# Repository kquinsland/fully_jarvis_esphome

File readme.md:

# Jarvis ESPHome

This is an extension / port of the initial reverse engineering work done by [@phord](https://github.com/phord) for the [`Jarvis`](https://github.com/phord/Jarvis) repo.
Rather than build everything from scratch, I have ported most of the functionality to an ESPHome component.

**Note:** You almost certainly should not use this ESPHome component! Thanks to [@maraid](https://github.com/maraid), more of the [UART has been reverse engineered](https://github.com/maraid/Jarvis#technical-notes). This means that the PCB is out of date and can be re-factored to simply interface with the desk via UART. This theoretically also means that ESPHome can control more aspects of the desk more precisely with fewer wires and a simpler software implementation!

## ESPHome Component

I am not a full time C++ programmer so the code almost certainly does look like a bad copy/paste job.
That's because it largely is! I found a few different "similar" projects and modeled my code off of those.

Details on how to use the custom component with ESPHome can be found in [components/fully_jarvis_cb2c](components/fully_jarvis_cb2c).

## PCB

Inspired by [this](https://github.com/phord/Jarvis/discussions/18) thread, I created a simple PCB to interface with the desk control / motor driver.
I used a more capable ESP32 module specifically so I could drive some RGBWW LED strips as well.

See the [cad](cad/readme.md) folder for the KiCad files.

The (mostly populated) PCB looks like this:

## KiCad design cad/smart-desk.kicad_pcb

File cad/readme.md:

# smart-desk-pcb

If you want to edit the pcb, the KiCad 6 files are included subject to [the license terms](../LICENSE.md).

The ESP32 module comes from [this](https://github.com/r0oland/ESP32_mini_KiCad_Library) library. Thanks to [r0oland](https://github.com/r0oland) for that library!

## BOM

The primary components on the PCB are:

- [D1 Mini style ESP32 chip](https://www.aliexpress.com/item/2251832633593063.html)
- [Configurable DC Buck converter module](https://www.aliexpress.com/item/32833398811.html). This steps the 12V dc from the KVM power supply down to the 5V for the ESP32 module.
- [RJ45 Jack (LCSC: C385834)](https://lcsc.com/product-detail/Ethernet-Connectors-Modular-Connectors-RJ45-RJ11_Ckmtw-Shenzhen-Cankemeng-R-RJ45R08P-A004_C385834.html). Footprint for this should be included in `jlcpcb.kicad_sym`. Two of theses for easy connection to the Jarvis remote/motor-controller.
- 2x5 ct [Diodes Incorporated DMN1019USN-7 (LCSC: C145103)](https://lcsc.com/product-detail/MOSFETs_Diodes-Incorporated-DMN1019USN-7_C145103.html). I had these handy and with the current ship shortage, it didn't seem worth th effort to try to source better ones. These are optional if you don't want the LED portion of the PCB.
- [Fuse holder (LCSC:C3131)](https://lcsc.com/product-detail/Fuse-Holders_Xucheng-Elec-C3131_C3131.html). Jump this out at your own risk!

There are some additional headers on the PCB for some optional components:

- PIR sensor (wired to ESP `gpio39`). I ended up not using this as I already have sufficient presence detection through other sensors placed around my home.
- An i2c based LIDAR sensor [`tof10120`](https://esphome.io/components/sensor/tof10120.html)) which I am using to measure distance from the desk to chair/person. Inclusion of this sensor was inspired by [this](.https://www.thouters.be/Standingstats.html) post from `Thomas Langewouters`.

## gerber

If you want to make zero changes, the [gerber files are included](./exports/2022-03.26.zip) and are subject to [the license terms](../LICENSE.md).

**Note**: There is a _small_ 'bug' with the v1 PCB: some of the MOSFETS do not have a connection to the ground plain. No, I don't know how this passed DRC. Fortunately, the fix is pretty easy: two small bodge wires connecting the GND pin from `U11` and `U15` to vias which connect to the ground plane.

**Note:** the two grey wires next to the fuse holder.

The gerber files / KiCad project are set up for use with JLCPCB but probably would work as-is with other PCB fab houses, too.

## Enclosure

I have included a STEP file export of the v1 PCB should you need it for PCB mounting hole locations or similar.

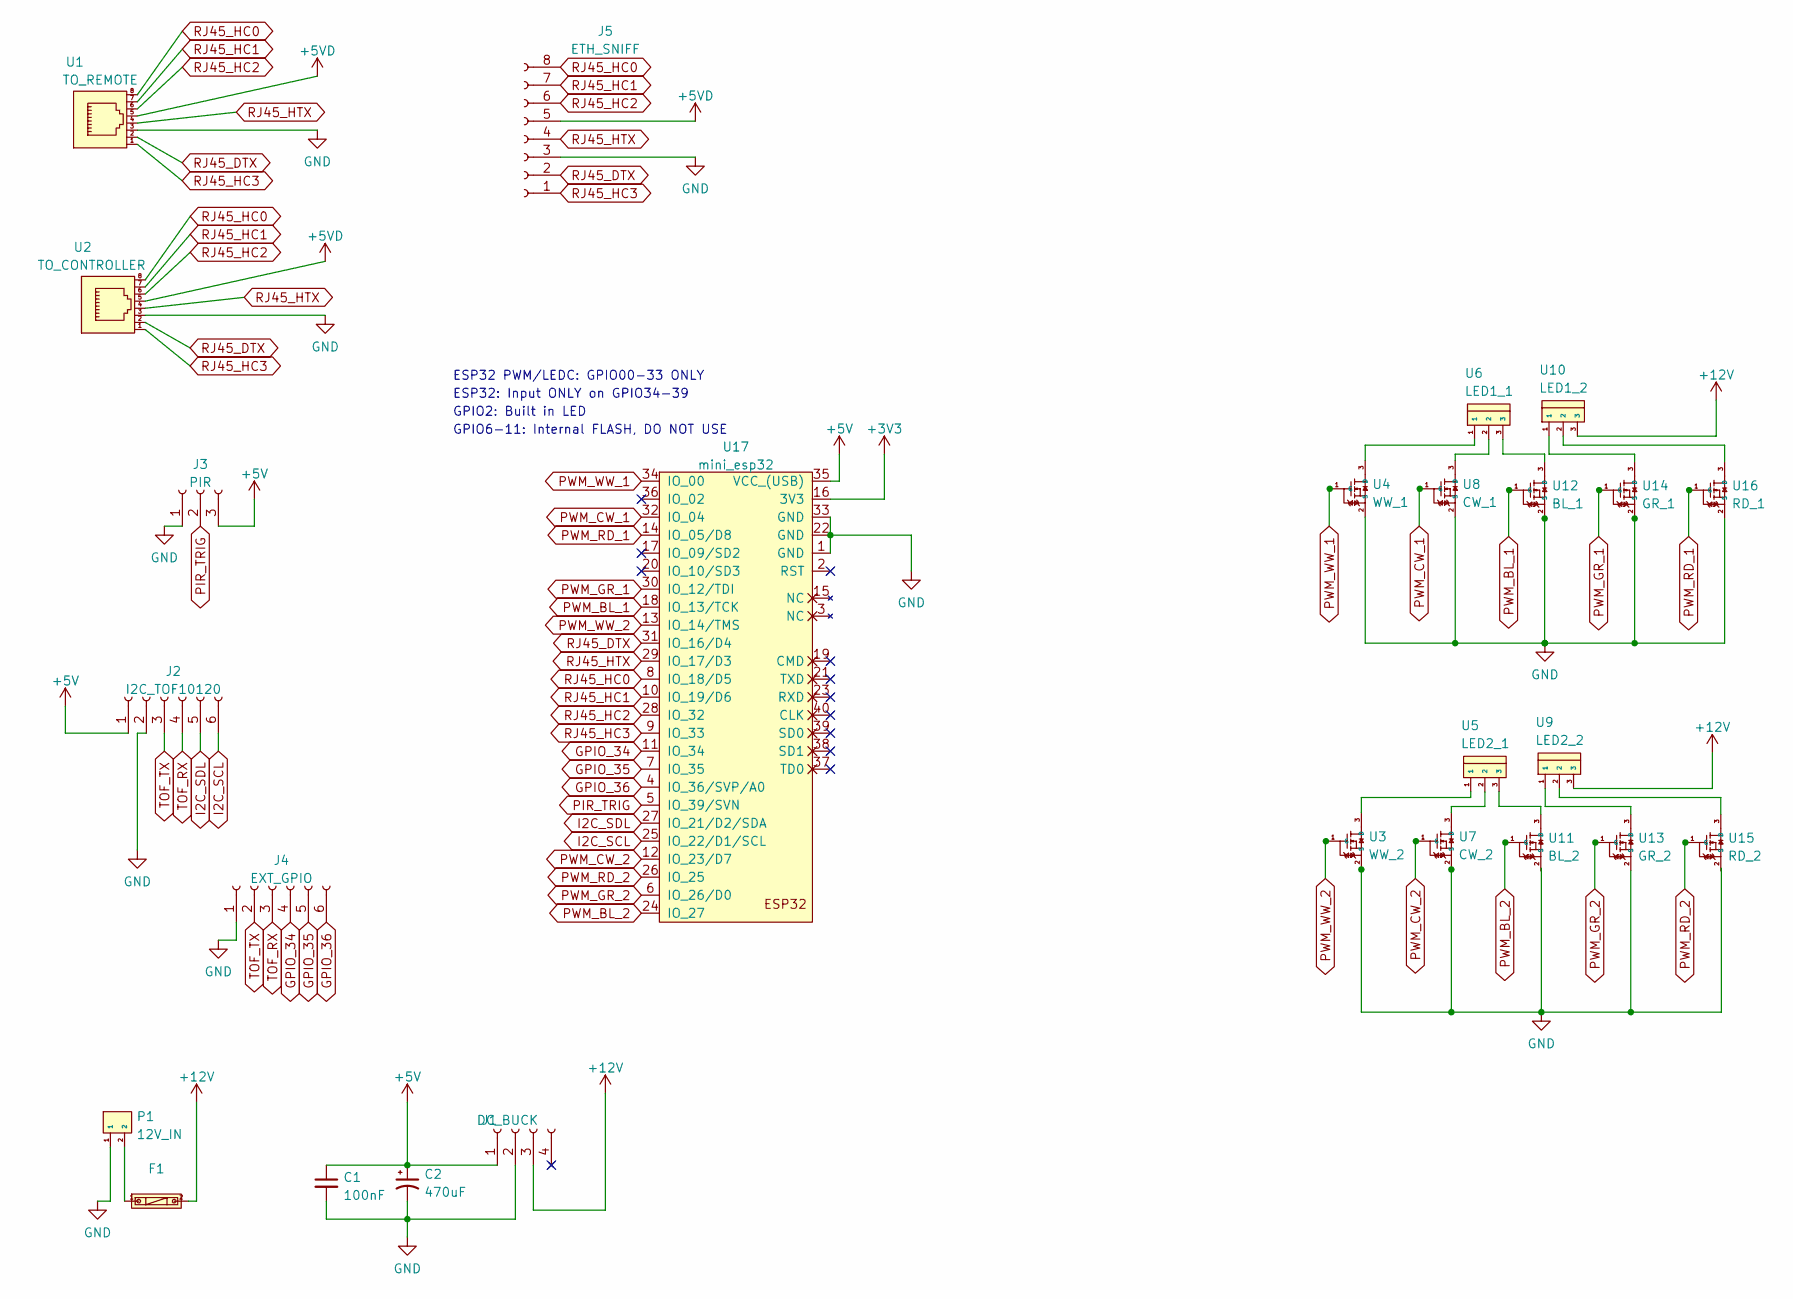
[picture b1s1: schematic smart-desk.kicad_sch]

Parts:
C1: 100nF; C_0805_2012Metric
C2: 470uF; C_Radial_D8.0mm_H11.5mm_P3.50mm
F1: 5x20_BLX-Atype_Fuse_holder_XC-7; C3131
J1: DC_BUCK; PinSocket_1x04_P2.54mm_Vertical
J2: I2C_TOF10120; PinSocket_1x06_P2.54mm_Vertical
J3: PIR; PinSocket_1x03_P2.54mm_Vertical
J4: EXT_GPIO; PinSocket_1x06_P2.54mm_Vertical
J5: ETH_SNIFF; PinSocket_1x08_P2.54mm_Vertical
P1: 12V_IN; WJ129V-5.0-2P
U1: TO_REMOTE; R-RJ45R08P-A004
U2: TO_CONTROLLER; R-RJ45R08P-A004
U3: WW_2; DMN1019USN-7
U4: WW_1; DMN1019USN-7
U5: LED2_1; 1757255
U6: LED1_1; 1757255
U7: CW_2; DMN1019USN-7
U8: CW_1; DMN1019USN-7
U9: LED2_2; 1757255
U10: LED1_2; 1757255
U11: BL_2; DMN1019USN-7
U12: BL_1; DMN1019USN-7
U13: GR_2; DMN1019USN-7
U14: GR_1; DMN1019USN-7
U15: RD_2; DMN1019USN-7
U16: RD_1; DMN1019USN-7
U17: mini_esp32; ESP32_mini

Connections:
+3V3: U17.16 (3V3)
+5VD: J5.5, U1.5, U2.5
+12V: F1.2, J1.3, U9.3, U10.3
GND: C1.2, C2.2, J1.2, J2.2, J3.1, J4.1, J5.3, P1.1, U1.3, U2.3, U3.2 (S), U4.2 (S), U7.2 (S), U8.2 (S), U12.2 (S), U13.2 (S), U14.2 (S), U16.2 (S), U17.1 (GND), U17.22 (GND), U17.33 (GND)
GPIO_34: J4.4, U17.11 (IO_34)
GPIO_35: J4.5, U17.7 (IO_35)
GPIO_36: J4.6, U17.4 (IO_36/SVP/A0)
I2C_SCL: J2.6, U17.25 (IO_22/D1/SCL)
I2C_SDL: J2.5, U17.27 (IO_21/D2/SDA)
unnamed: F1.1, P1.2
unnamed: U3.3 (D), U5.1
unnamed: U4.3 (D), U6.1
unnamed: U5.2, U7.3 (D)
unnamed: U6.2, U8.3 (D)
unnamed: U10.1, U14.3 (D)
unnamed: U10.2, U16.3 (D)
unnamed: U5.3, U11.3 (D)
unnamed: U6.3, U12.3 (D)
unnamed: U9.1, U13.3 (D)
unnamed: U9.2, U15.3 (D)
PIR_TRIG: J3.2, U17.5 (IO_39/SVN)
PWM_BL_1: U12.1 (G), U17.18 (IO_13/TCK)
PWM_BL_2: U11.1 (G), U17.24 (IO_27)
PWM_CW_1: U8.1 (G), U17.32 (IO_04)
PWM_CW_2: U7.1 (G), U17.12 (IO_23/D7)
PWM_GR_1: U14.1 (G), U17.30 (IO_12/TDI)
PWM_GR_2: U13.1 (G), U17.6 (IO_26/D0)
PWM_RD_1: U16.1 (G), U17.14 (IO_05/D8)
PWM_RD_2: U15.1 (G), U17.26 (IO_25)
PWM_WW_1: U4.1 (G), U17.34 (IO_00)
PWM_WW_2: U3.1 (G), U17.13 (IO_14/TMS)
RJ45_DTX: J5.2, U1.2, U2.2, U17.31 (IO_16/D4)
RJ45_HC0: J5.8, U1.8, U2.8, U17.8 (IO_18/D5)
RJ45_HC1: J5.7, U1.7, U2.7, U17.10 (IO_19/D6)
RJ45_HC2: J5.6, U1.6, U2.6, U17.28 (IO_32)
RJ45_HC3: J5.1, U1.1, U2.1, U17.9 (IO_33)
RJ45_HTX: J5.4, U1.4, U2.4, U17.29 (IO_17/D3)
TOF_RX: J2.4, J4.3
TOF_TX: J2.3, J4.2

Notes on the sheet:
ESP32 PWM/LEDC: GPIO00-33 ONLY
ESP32: Input ONLY on GPIO34-39
GPIO2: Built in LED
GPIO6-11: Internal FLASH, DO NOT USE

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
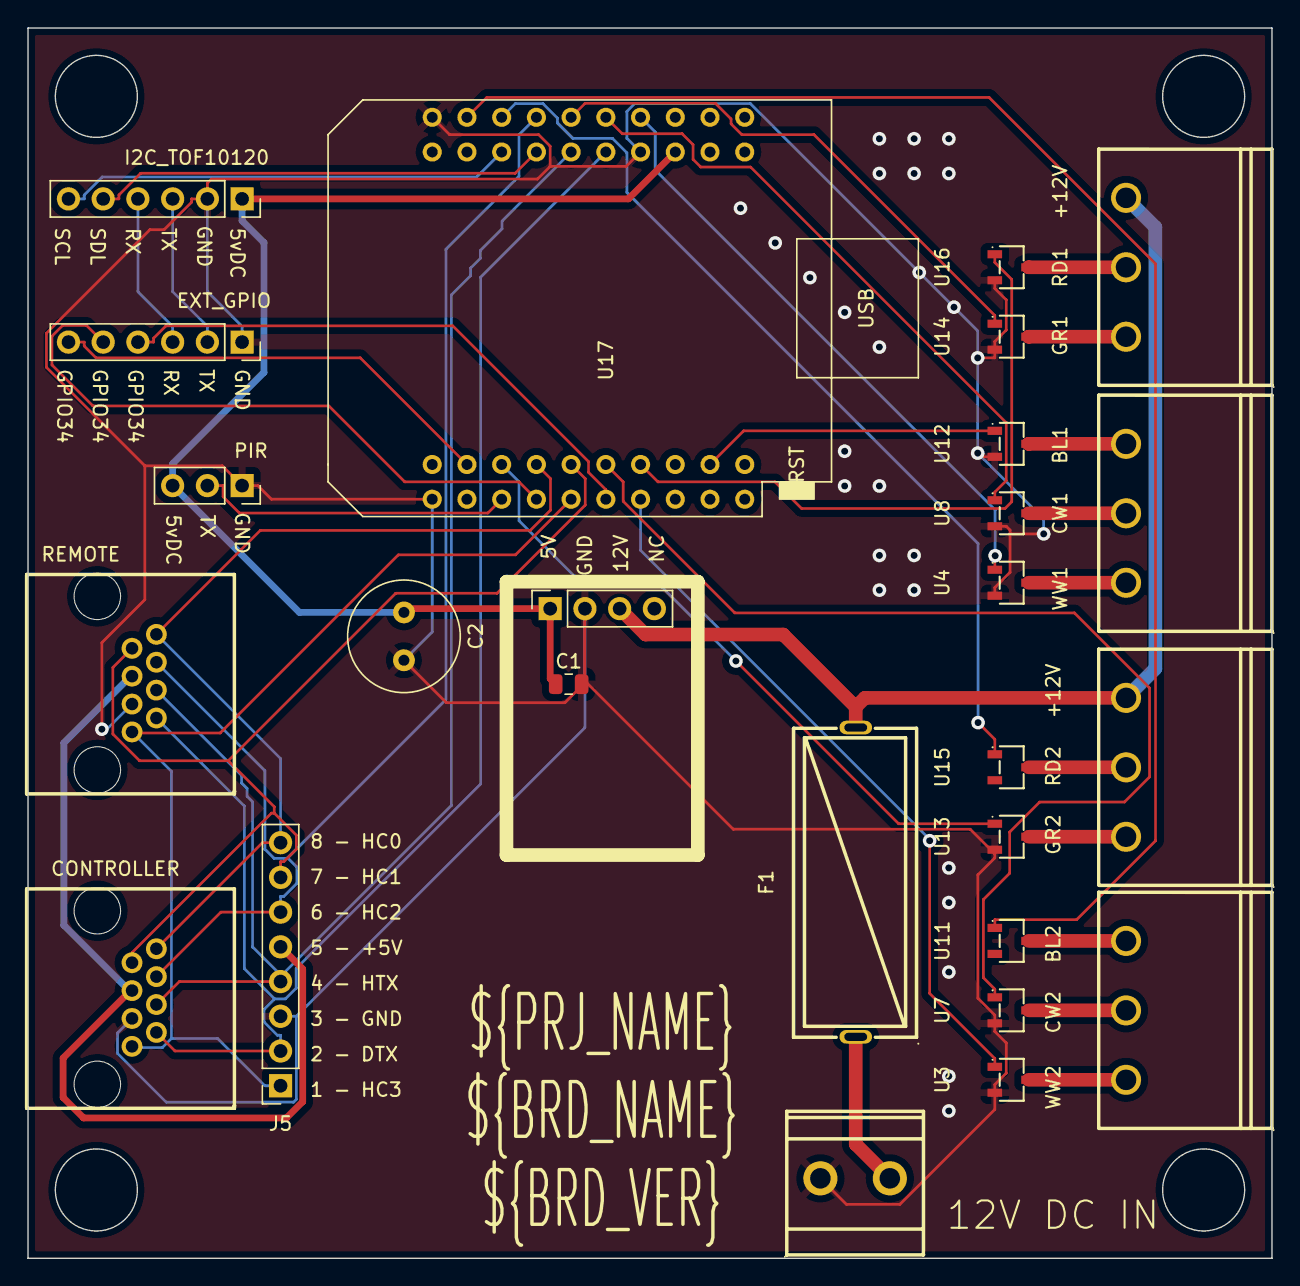
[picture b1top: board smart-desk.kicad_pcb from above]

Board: 2 copper layers, 91.0 x 90.0 mm, 26 parts (0 on the bottom side), 39 nets.

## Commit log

2022-06-03 initial
2022-06-03 Add some dotfiles
2022-06-03 Add PCB readme
    and installed photo w/ bodge wires
2022-06-03 Add GERBER exports
    and update main readme to include pic
2022-06-03 Add example yaml for custom component
